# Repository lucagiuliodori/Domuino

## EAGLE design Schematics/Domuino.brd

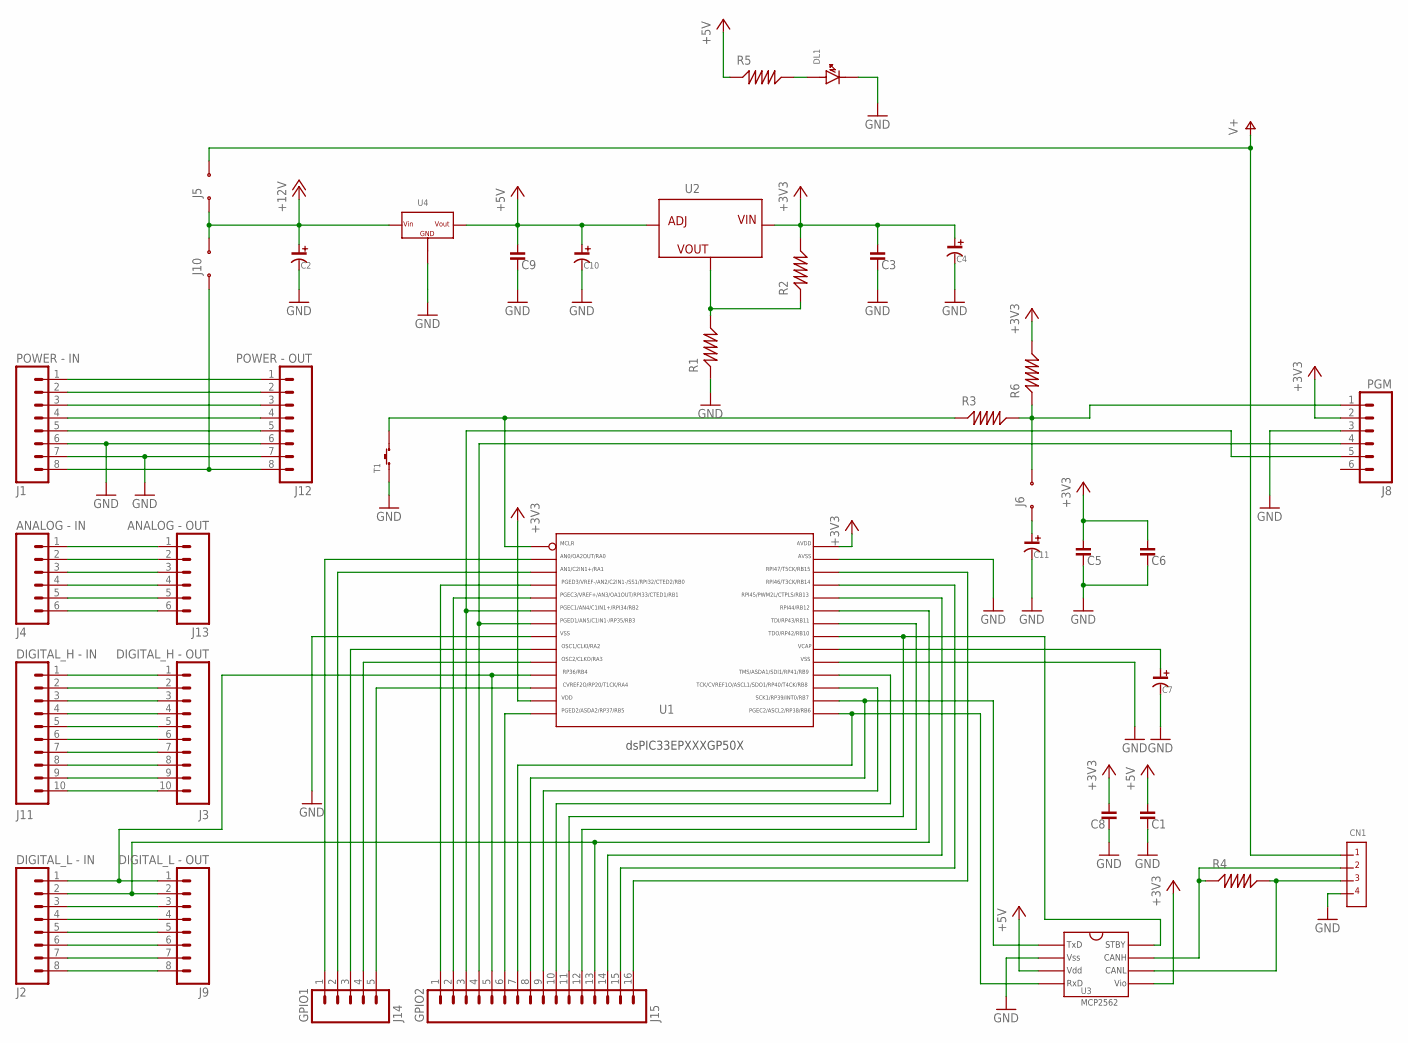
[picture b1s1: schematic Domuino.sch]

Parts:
C1, C3, C5, C6, C8, C9: 0,1u; C_P5
C2: 1u; E_P5_D10
C4, C10: 1u; E_P5_D8
C7: 10u; SIZEB
C11: 10u; E_P2_D5
CN1: MORS_4VIE_P.3.5; MORS_4V_P3.5
DL1: ROSSO; DIODO_3MM_TRAD.
J1: POWER - IN; 1X08_ROUND
J2: DIGITAL_L - IN; 1X08_ROUND
J3: DIGITAL_H - OUT; 1X10
J4: ANALOG - IN; 1X06
J5, J6, J10: JUMPER_2VIE_TRAD; JUMPER(2V)
J8: PGM; 1X06
J9: DIGITAL_L - OUT; 1X08_ROUND
J11: DIGITAL_H - IN; 1X10
J12: POWER - OUT; 1X08_ROUND
J13: ANALOG - OUT; 1X06
J14: GPIO1; 1X05
J15: GPIO2; 1X16
R1: 3,3k; R_TRAD_P10
R2: 5,6k; R_TRAD_P10
R3, R6: 10k; R_TRAD_P10
R4: 120; R_TRAD_P10
R5: 150; R_TRAD_P10
T1: PULSANTE_EVQ_PAG_07M; EVQ_PAG_07M
U1: DSPIC33EPXXXGP50X_SPDIP; SPDIP-28PIN
U2: LM317; TO220
U3: MCP2562_DIL08; DIL08_P7.5
U4: LM7805; TO220

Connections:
+3V3: C3.P$1 (1), C4.P$1, C5.P$1 (1), C6.P$1 (1), C8.P$1 (1), J8.2, R2.P$2, R6.P$2, U1.P$13, U1.P$28, U2.P$3 (IN), U3.P$5
+5V: C1.P$1 (1), C9.P$1 (1), C10.P$1, R5.P$1, U2.P$1 (ADJ), U3.P$3, U4.P$3 (VOUT)
+12V: C2.P$1, J5.P$1, J10.P$2, U4.P$1 (VIN)
GND: C1.P$2 (2), C2.P$2, C3.P$2 (2), C4.P$2, C5.P$2 (2), C6.P$2 (2), C7.P$3, C8.P$2 (2), C9.P$2 (2), C10.P$2, C11.P$2, CN1.P$4, DL1.P$1 (K), J1.6, J1.7, J8.3, J12.6, J12.7, R1.P$1, T1.P$1, T1.P$4, U1.P$8, U1.P$19, U1.P$27, U3.P$2, U4.P$2 (GND)
unnamed: J1.8, J10.P$1, J12.8
unnamed: R1.P$2, R2.P$1, U2.P$2 (OUT)
unnamed: J4.4, J13.4
unnamed: C11.P$1, J6.P$1
unnamed: J4.5, J13.5
unnamed: J4.6, J13.6
unnamed: R3.P$1, T1.P$2, T1.P$3, U1.P$1
unnamed: J8.5, J15.3, U1.P$6
unnamed: J8.4, J15.4, U1.P$7
unnamed: CN1.P$2, R4.P$1, U3.P$7
unnamed: CN1.P$3, R4.P$2, U3.P$6
unnamed: J15.8, U1.P$16, U3.P$1
unnamed: J15.7, U1.P$15, U3.P$4
unnamed: J3.1, J11.1
unnamed: J15.11, U1.P$21, U3.P$8
unnamed: J6.P$2, J8.1, R3.P$2, R6.P$1
unnamed: J3.2, J11.2
unnamed: J3.3, J11.3
unnamed: J3.4, J11.4
unnamed: J3.5, J11.5
unnamed: J3.6, J11.6
unnamed: J3.7, J11.7
unnamed: J3.8, J11.8
unnamed: J3.9, J11.9
unnamed: J3.10, J11.10
unnamed: J2.1, J9.1, J15.5, U1.P$11
unnamed: C7.P$2, U1.P$20
unnamed: J15.14, U1.P$24
unnamed: J2.3, J9.3
unnamed: J2.4, J9.4
unnamed: J2.5, J9.5
unnamed: J2.6, J9.6
unnamed: J2.7, J9.7
unnamed: J2.8, J9.8
unnamed: J1.1, J12.1
unnamed: J1.2, J12.2
unnamed: J1.3, J12.3
unnamed: J1.4, J12.4
unnamed: J1.5, J12.5
unnamed: J4.1, J13.1
unnamed: J4.2, J13.2
unnamed: J4.3, J13.3
unnamed: J14.5, U1.P$12
unnamed: J14.4, U1.P$10
unnamed: J14.3, U1.P$9
unnamed: J14.2, U1.P$3
unnamed: J14.1, U1.P$2
unnamed: J15.1, U1.P$4
unnamed: J15.2, U1.P$5
unnamed: J15.6, U1.P$14
unnamed: J15.12, U1.P$22
unnamed: J15.9, U1.P$17
unnamed: J15.10, U1.P$18
unnamed: J2.2, J9.2, J15.13, U1.P$23
unnamed: J15.15, U1.P$25
unnamed: J15.16, U1.P$26
unnamed: DL1.P$2 (A), R5.P$2
V+: CN1.P$1, J5.P$2

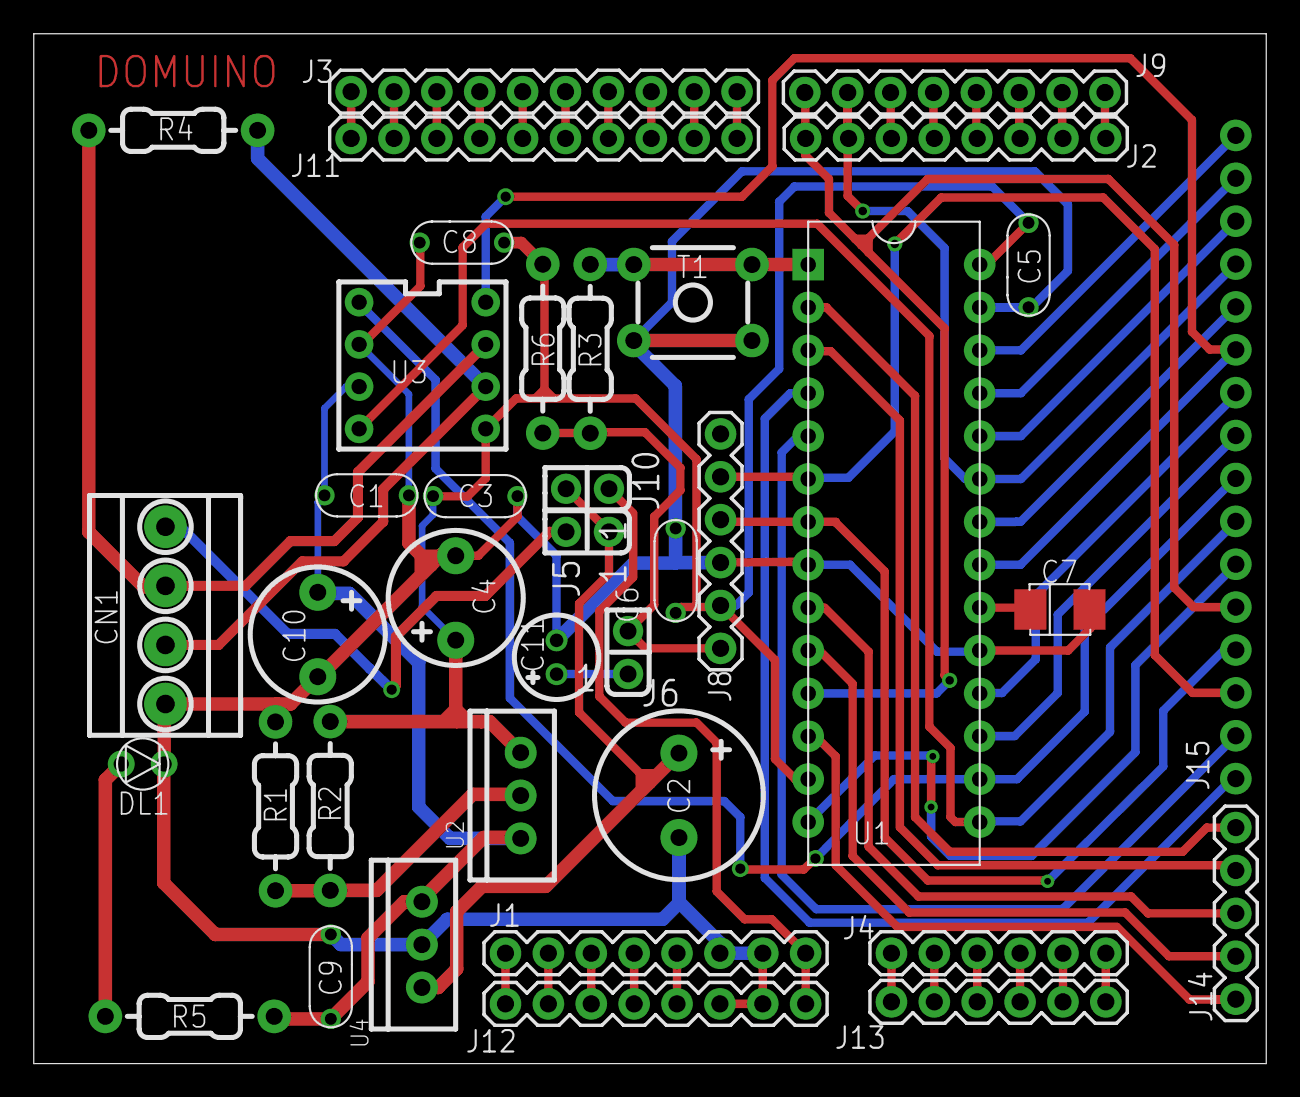
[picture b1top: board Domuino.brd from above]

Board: 2 copper layers, 73.0 x 61.0 mm, 38 parts (1 on the bottom side), 62 nets.

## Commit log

2017-08-17 My First Commit
2017-08-18 Paths change

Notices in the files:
parts and their libraries:
SparkFun-Connectors: Licensing: Creative Commons ShareAlike 4.0 International - https://creativecommons.org/licenses/by-sa/4.0
